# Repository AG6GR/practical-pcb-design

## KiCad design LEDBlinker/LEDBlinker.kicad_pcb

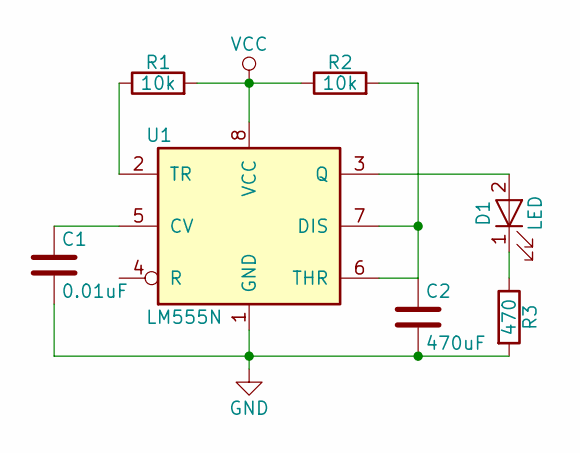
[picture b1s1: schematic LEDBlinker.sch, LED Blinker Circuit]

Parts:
C1: 0.01uF; C_Radial_D5_L6_P2.5
C2: 470uF; C_Radial_D5_L6_P2.5
D1: LED; LED-5MM
R1, R2: 10k; Resistor_Horizontal_RM7mm
R3: 470; Resistor_Horizontal_RM7mm
U1: LM555N; DIP-8_W7.62mm_Socket

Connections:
GND: C1.2, C2.2, R3.2, U1.1 (GND)
unnamed: C1.1, U1.5 (CV)
unnamed: C2.1, R2.2, U1.6 (THR), U1.7 (DIS)
unnamed: D1.1 (K), R3.1
unnamed: D1.2 (A), U1.3 (Q)
unnamed: R1.1, U1.2 (TR)
VCC: R1.2, R2.1, U1.8 (VCC)

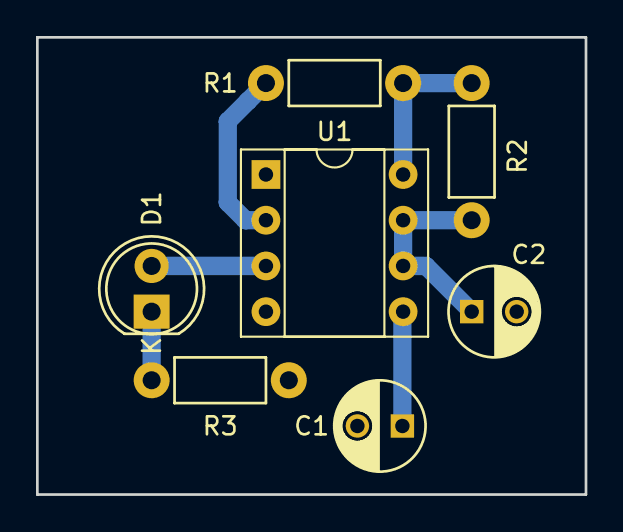
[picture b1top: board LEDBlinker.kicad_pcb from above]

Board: 2 copper layers, 30.5 x 25.4 mm, 7 parts (0 on the bottom side), 7 nets.

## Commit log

2017-04-22 Add to version control
2017-04-22 Finish schematic
2017-04-24 Functional complete first draft
2017-04-24 Add title page
